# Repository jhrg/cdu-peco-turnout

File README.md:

PECO PL-10 Turnout motor Capacitive Discharge Unit PCB

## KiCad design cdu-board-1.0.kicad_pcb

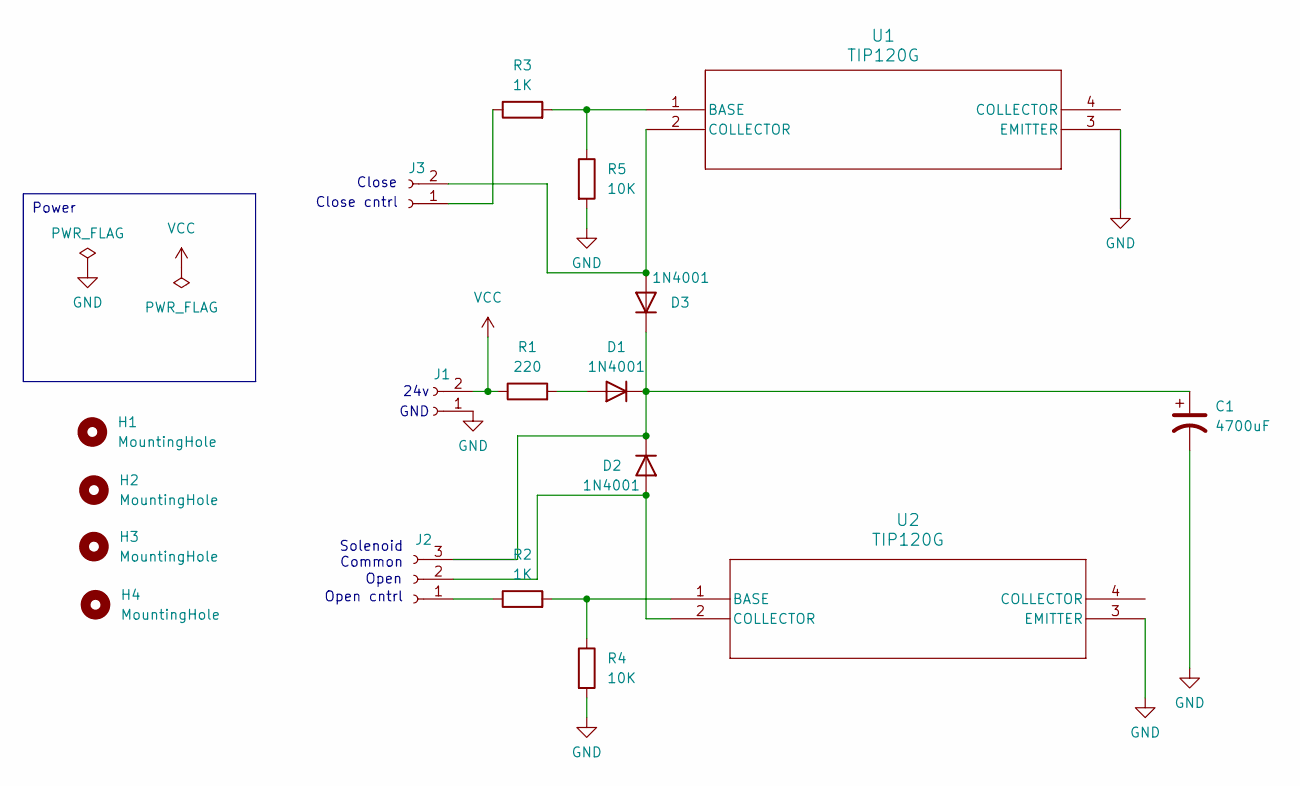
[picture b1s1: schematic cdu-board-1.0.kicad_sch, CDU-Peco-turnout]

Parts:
C1: 4700uF; PCAP_18x355_PAN
D1, D2, D3: 1N4001; D_T-1_P10.16mm_Horizontal
H1, H2, H3, H4: MountingHole; MountingHole_3mm
J1, J3: Conn_01x02_Socket; CONN_OSTVN02A150_OST
J2: Conn_01x03_Socket; CONN3_OSTVN03A150_OST
R1: 220; R_Axial_DIN0617_L17.0mm_D6.0mm_P7.62mm_Vertical
R2, R3: 1K; YAG_CFR25_YAG
R4, R5: 10K; YAG_CFR25_YAG
U1, U2: TIP120G; TO-220-3_10P53X15P75_ONS

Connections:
GND: C1.2, J1.1, R4.2, R5.2, U1.3 (EMITTER), U2.3 (EMITTER)
unnamed: D1.2 (A), R1.2
unnamed: C1.1, D1.1 (K), D2.1 (K), D3.1 (K), J2.3
unnamed: D2.2 (A), J2.2, U2.2 (COLLECTOR)
unnamed: D3.2 (A), J3.2, U1.2 (COLLECTOR)
unnamed: J2.1, R2.1
unnamed: J3.1, R3.1
unnamed: R3.2, R5.1, U1.1 (BASE)
unnamed: R2.2, R4.1, U2.1 (BASE)
VCC: J1.2, R1.1

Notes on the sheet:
Power
Close
Close cntrl
Open cntrl
GND
Solenoid Common
Open
24v

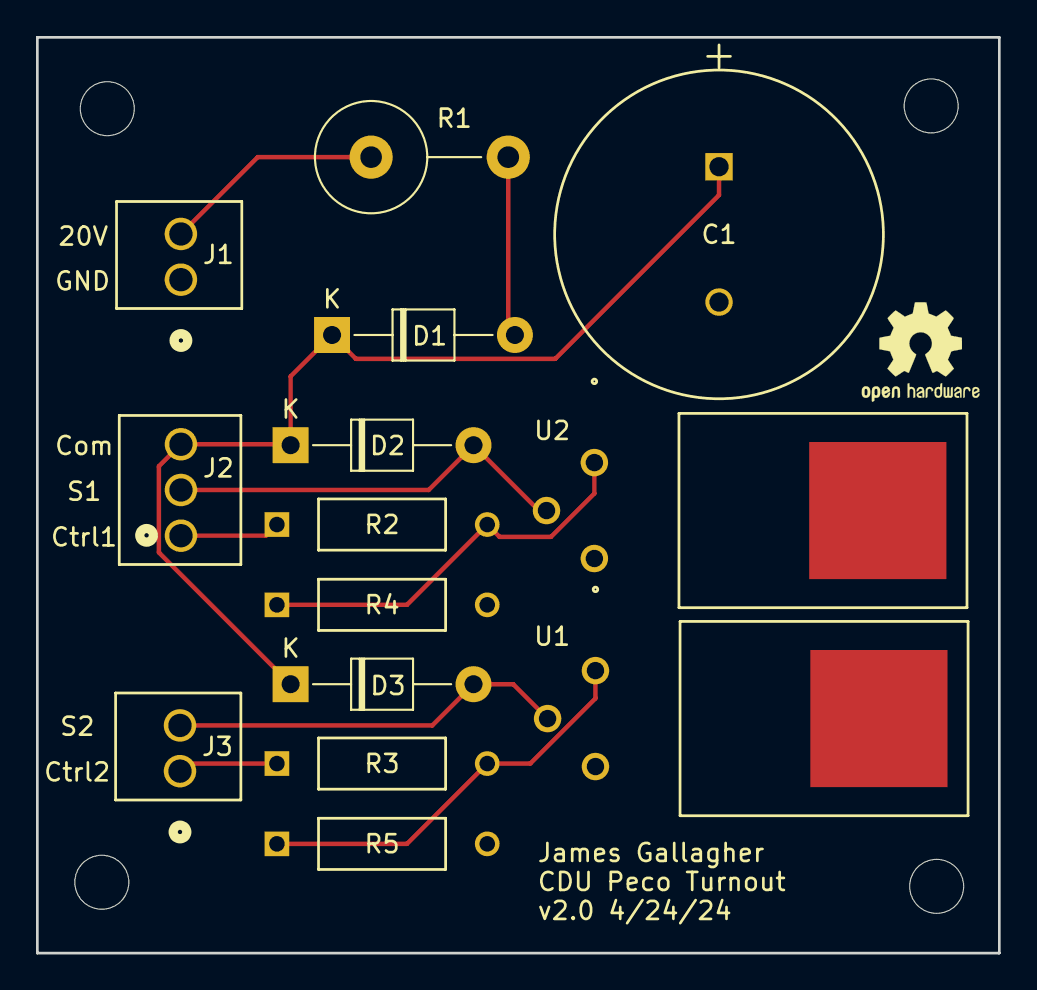
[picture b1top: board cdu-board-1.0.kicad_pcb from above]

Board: 2 copper layers, 53.4 x 50.9 mm, 18 parts (0 on the bottom side), 10 nets.

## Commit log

2024-04-25 Fixed transistor - v1.0 used TIP220G and not TIP120G
2024-04-25 Added QR code, fixed an error
2024-04-26 Added QR code
